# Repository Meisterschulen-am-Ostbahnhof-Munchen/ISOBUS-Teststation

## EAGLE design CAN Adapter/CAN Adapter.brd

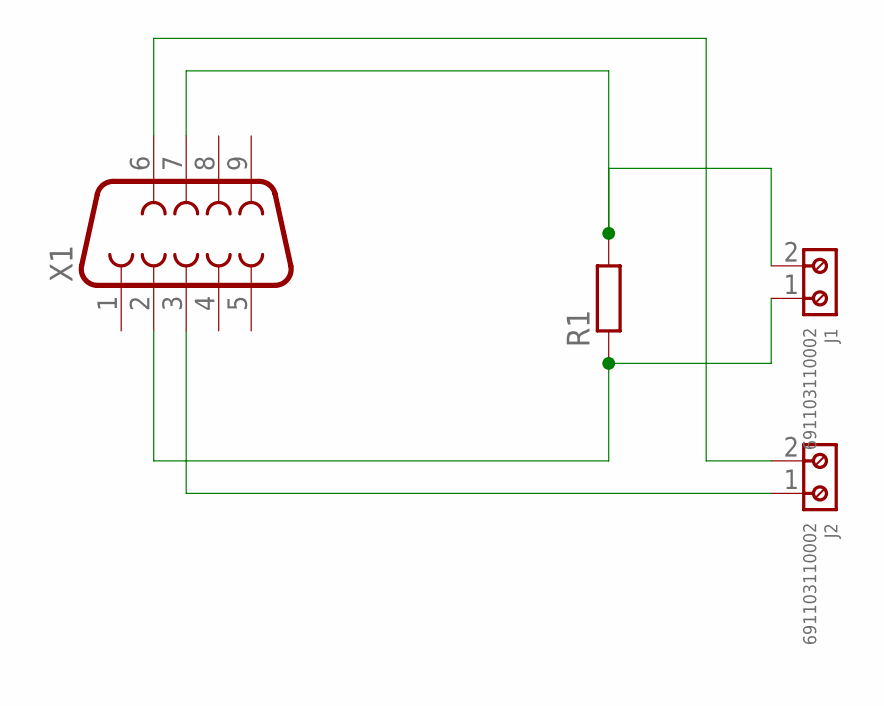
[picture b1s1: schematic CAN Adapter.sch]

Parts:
J1, J2: 691103110002
R1: R-EU_0204/7; 0204/7
X1: F09D

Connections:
unnamed: J1.1, R1.1, X1.2
unnamed: J1.2, R1.2, X1.7
unnamed: J2.1, X1.3
unnamed: J2.2, X1.6

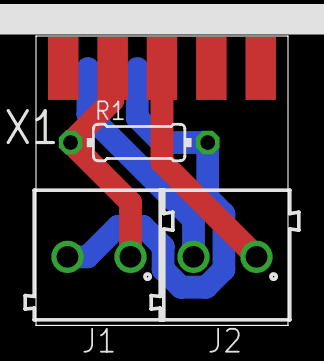
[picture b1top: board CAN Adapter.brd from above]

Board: 2 copper layers, 14.0 x 16.1 mm, 4 parts (0 on the bottom side), 4 nets.

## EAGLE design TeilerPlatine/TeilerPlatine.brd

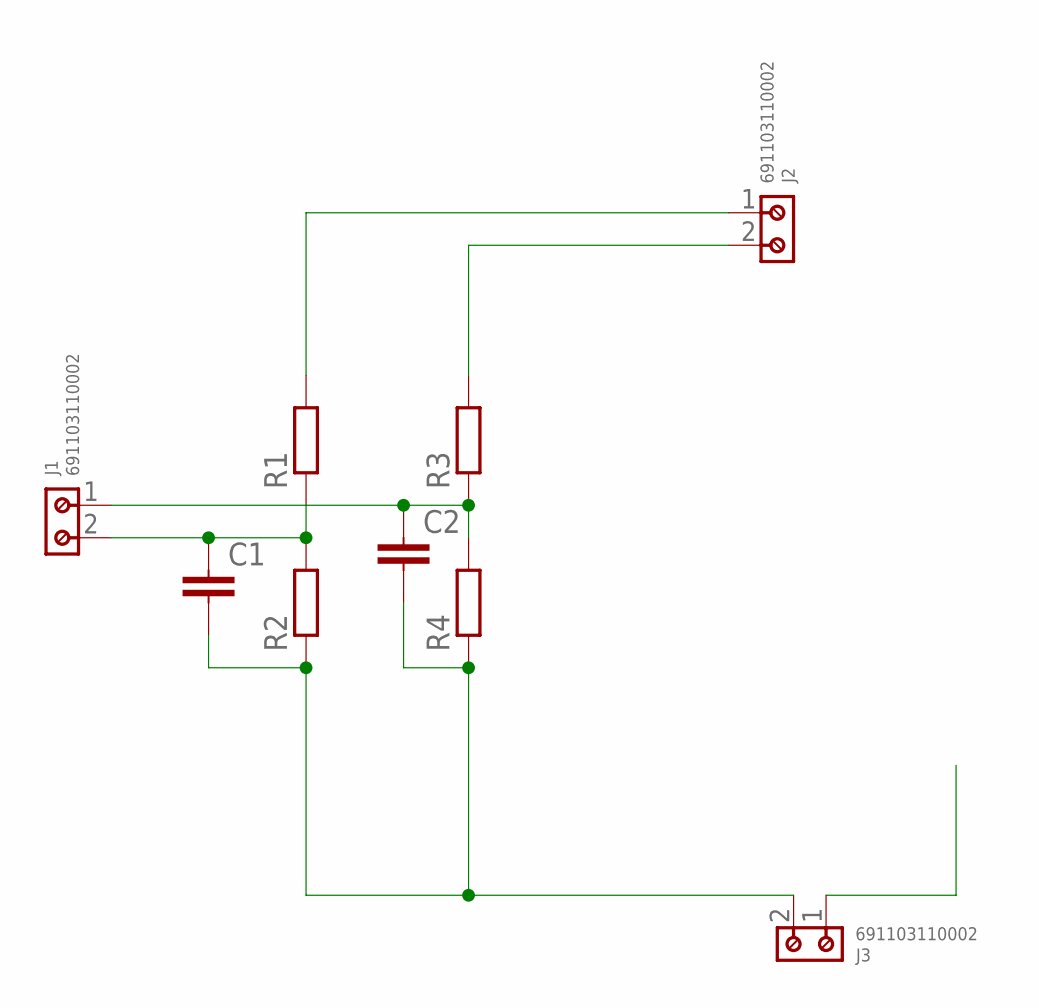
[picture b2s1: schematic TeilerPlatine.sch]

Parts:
C1, C2: C-EU050-025X075; C050-025X075
J1, J2, J3: 691103110002
R1, R2, R3, R4: R-EU_0411/15; 0411/15

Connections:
unnamed: C1.2, C2.2, J3.2, R2.1, R4.1
unnamed: J2.1, R1.2
unnamed: J2.2, R3.2
unnamed: C1.1, J1.2, R1.1, R2.2
unnamed: C2.1, J1.1, R3.1, R4.2

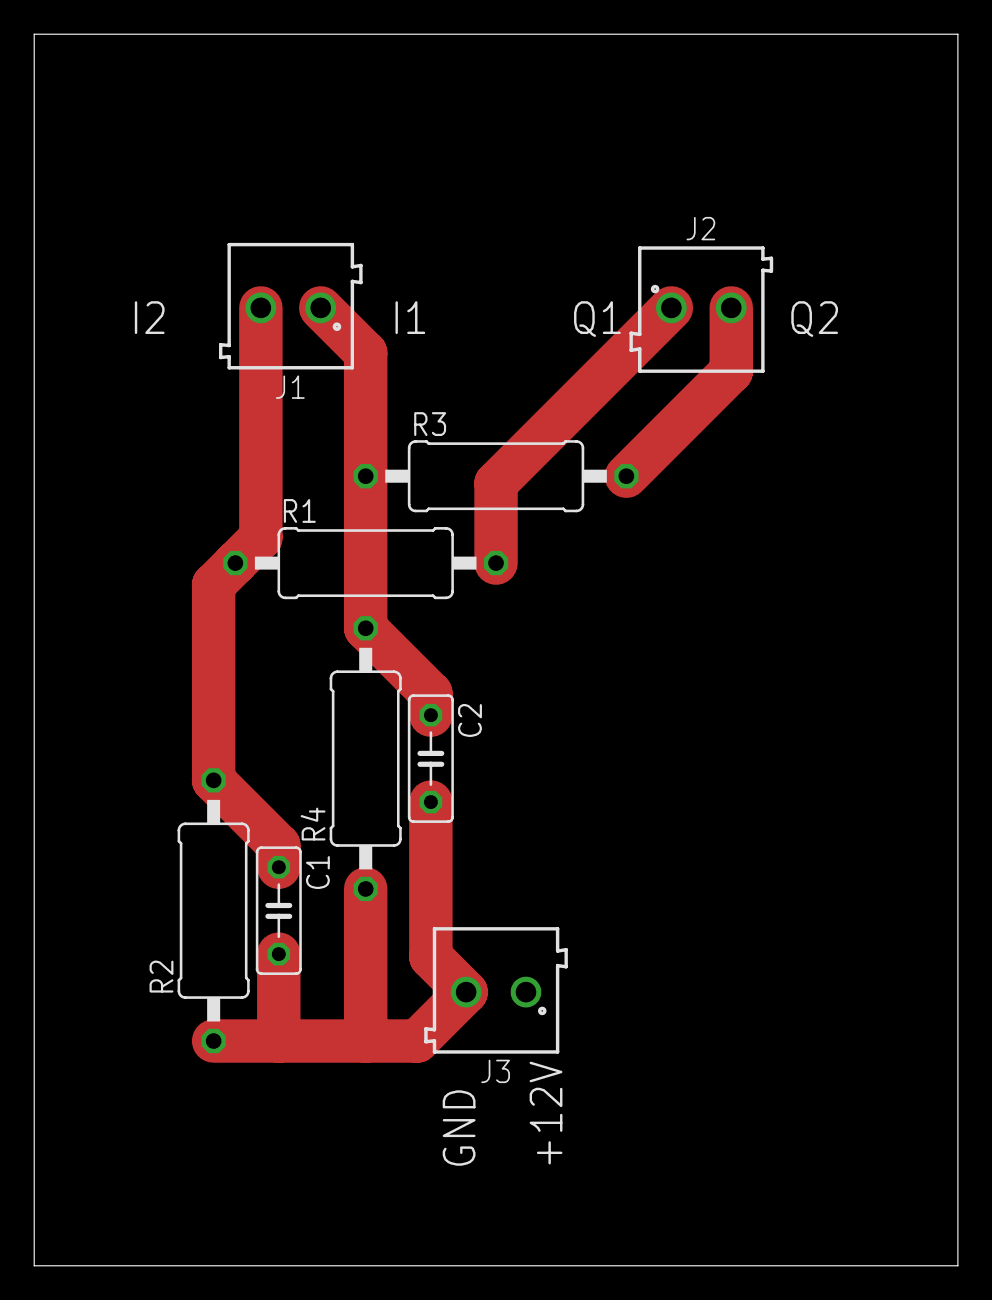
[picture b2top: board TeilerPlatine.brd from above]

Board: 2 copper layers, 54.0 x 72.0 mm, 9 parts (0 on the bottom side), 5 nets.

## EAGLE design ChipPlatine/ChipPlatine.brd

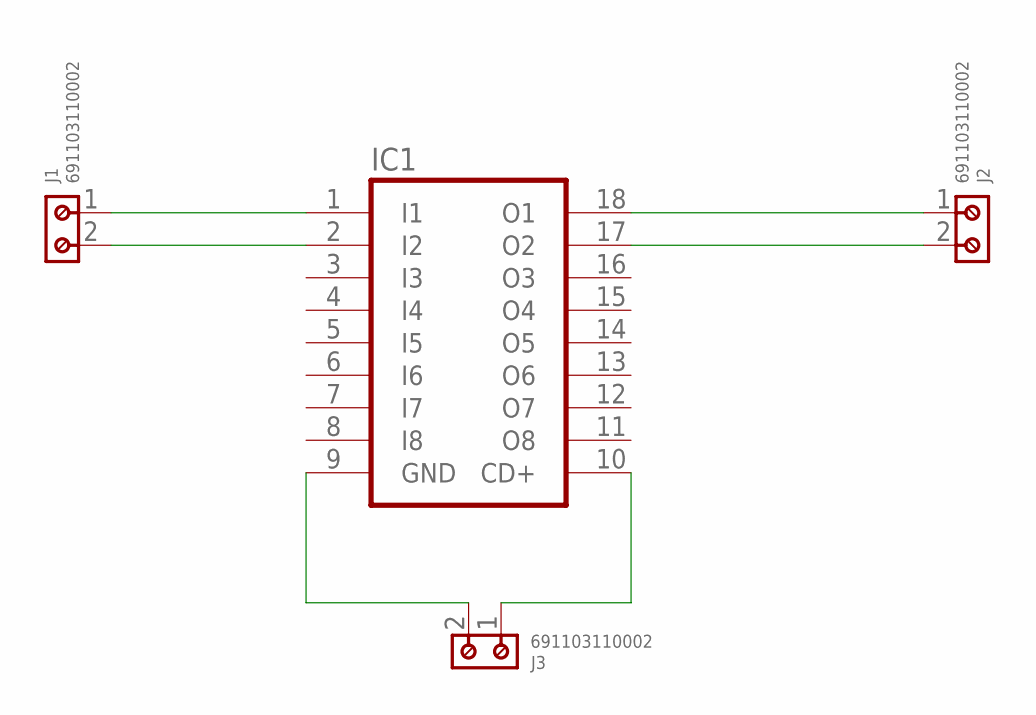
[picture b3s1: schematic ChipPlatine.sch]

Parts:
IC1: ULN2803A; DIL18
J1, J2, J3: 691103110002

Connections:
unnamed: IC1.1 (I1), J1.1
unnamed: IC1.2 (I2), J1.2
unnamed: IC1.18 (O1), J2.1
unnamed: IC1.17 (O2), J2.2
unnamed: IC1.9 (GND), J3.2
unnamed: IC1.10 (CD+), J3.1

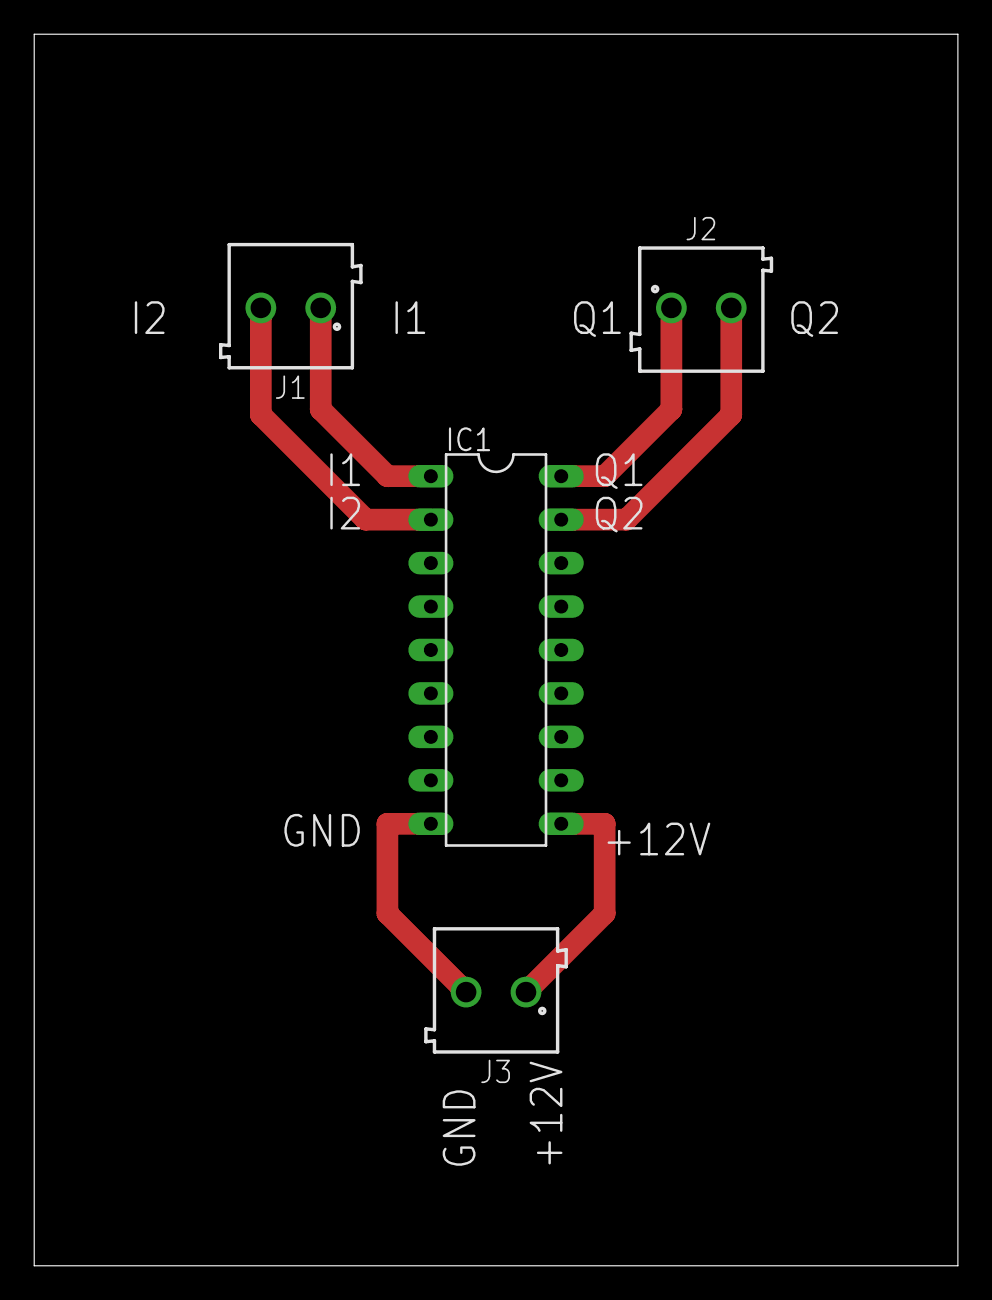
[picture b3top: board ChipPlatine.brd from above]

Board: 2 copper layers, 54.0 x 72.0 mm, 4 parts (0 on the bottom side), 6 nets.

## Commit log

2023-06-13 all PCBs
2023-06-13 Mounts

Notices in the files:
parts and their libraries:
Wurth_Connectors_WR-TBL Wire Protector: Copyright: Würth Elektronik
